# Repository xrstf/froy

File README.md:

# Frøy - ESP8266+BME Hygrometer

This repository contains the source code, schematics and everything else for my
personal fancy homegrown hygrometer (sensor that reports temperature, humidity and
pressure).

## Features

* push or pull mode
* supports BME280, BME680 and BMP280 chips
* programming via USB (only for indoor variant, others need a standalone USB->UART converter)
* webserver with Prometheus compatible `/metrics` endpoint
* reconfiguration via USB or WiFi (i.e. `curl -XPOST -d'{"new":"config"}' http://device/`)
* OTA pull support (Frøy pulls new firmware from a specified location)
* TLS support (single fingerprint only)
* relatively easy to solder by hand (nothing smaller than an 0805 package)

## Mode of Operation

Both indoor and outdoor versions can work in one of two modes:

* **Pull Mode** ("server mode") -- in this mode, Frøy is constantly running and connected
  to your WiFi. It provides an HTTP server and expects you to fetch the data whenever
  you need it (for example via Prometheus).
* **Push Mode** -- in this mode, Frøy will make a measurement, connect to WiFi, send out the
  data to a preconfigured URL and then go to sleep for a configurable amount of time. Rinse
  and repeat.

The advantage of the Pull Mode is that the interval can be centralled controlled (if you have
multiple devices). It also makes it easier to trigger an OTA, as Frøy is constantly listening
for requests.

The advantage of the Push Mode is that Frøy doesn't need any Firewall rules to be reachable
and it saves power (critical for the Outdoor version). Also, indoor versions in Pull Mode would
considerable heat up (an ESP8266 that is connected to WiFi can be 35-40°C) and skew the sensor
readings. So even for indoor versions it is advisable to use Push Mode instead.

While Frøy is not reachable in Push Mode (it never starts a webserver and you'd be pretty luck
to send a request to it the moment it wakes up and before it goes back to sleep), it is still
possible to reconfigurable Frøy remotely by putting the new configuration in the _response_ to
Frøy's push request.

## Flavors

Frøy currently comes in three flavors:

### Frøy Outdoor

This is the original project. It runs using a CR123 battery, which lasts roughly 3-5
months when reporting data every 15 minutes.

The case can be bought on Amazon: https://www.amazon.de/gp/product/B072M2JKGW/ -- I am not
aware of any alternative sources. In case the product disappears, I saved the schematics
in `docs/images/froy-outdoor-case-drawings.jpg`.

### Frøy Indoor

This variant is powered by USB and suitable for indoor use.

### Froy ForMen

This variant is powered by mains voltage and is suitable for locations where changing
the battery regularly is not desirable.

The case can be bought on Amazon, for example https://www.amazon.de/gp/product/B07B9KY9X4/ --
alternatively search for "Snowsound case" on your favorite search engine.

---

Frøy was named after the character in the NRK series ["Norsemen"](https://tv.nrk.no/serie/vikingane).

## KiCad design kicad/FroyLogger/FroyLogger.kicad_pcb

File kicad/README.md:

# KiCad Designs

These designs require that https://github.com/xrstf/kicad-library is set up in your
local KiCad 5 installation.

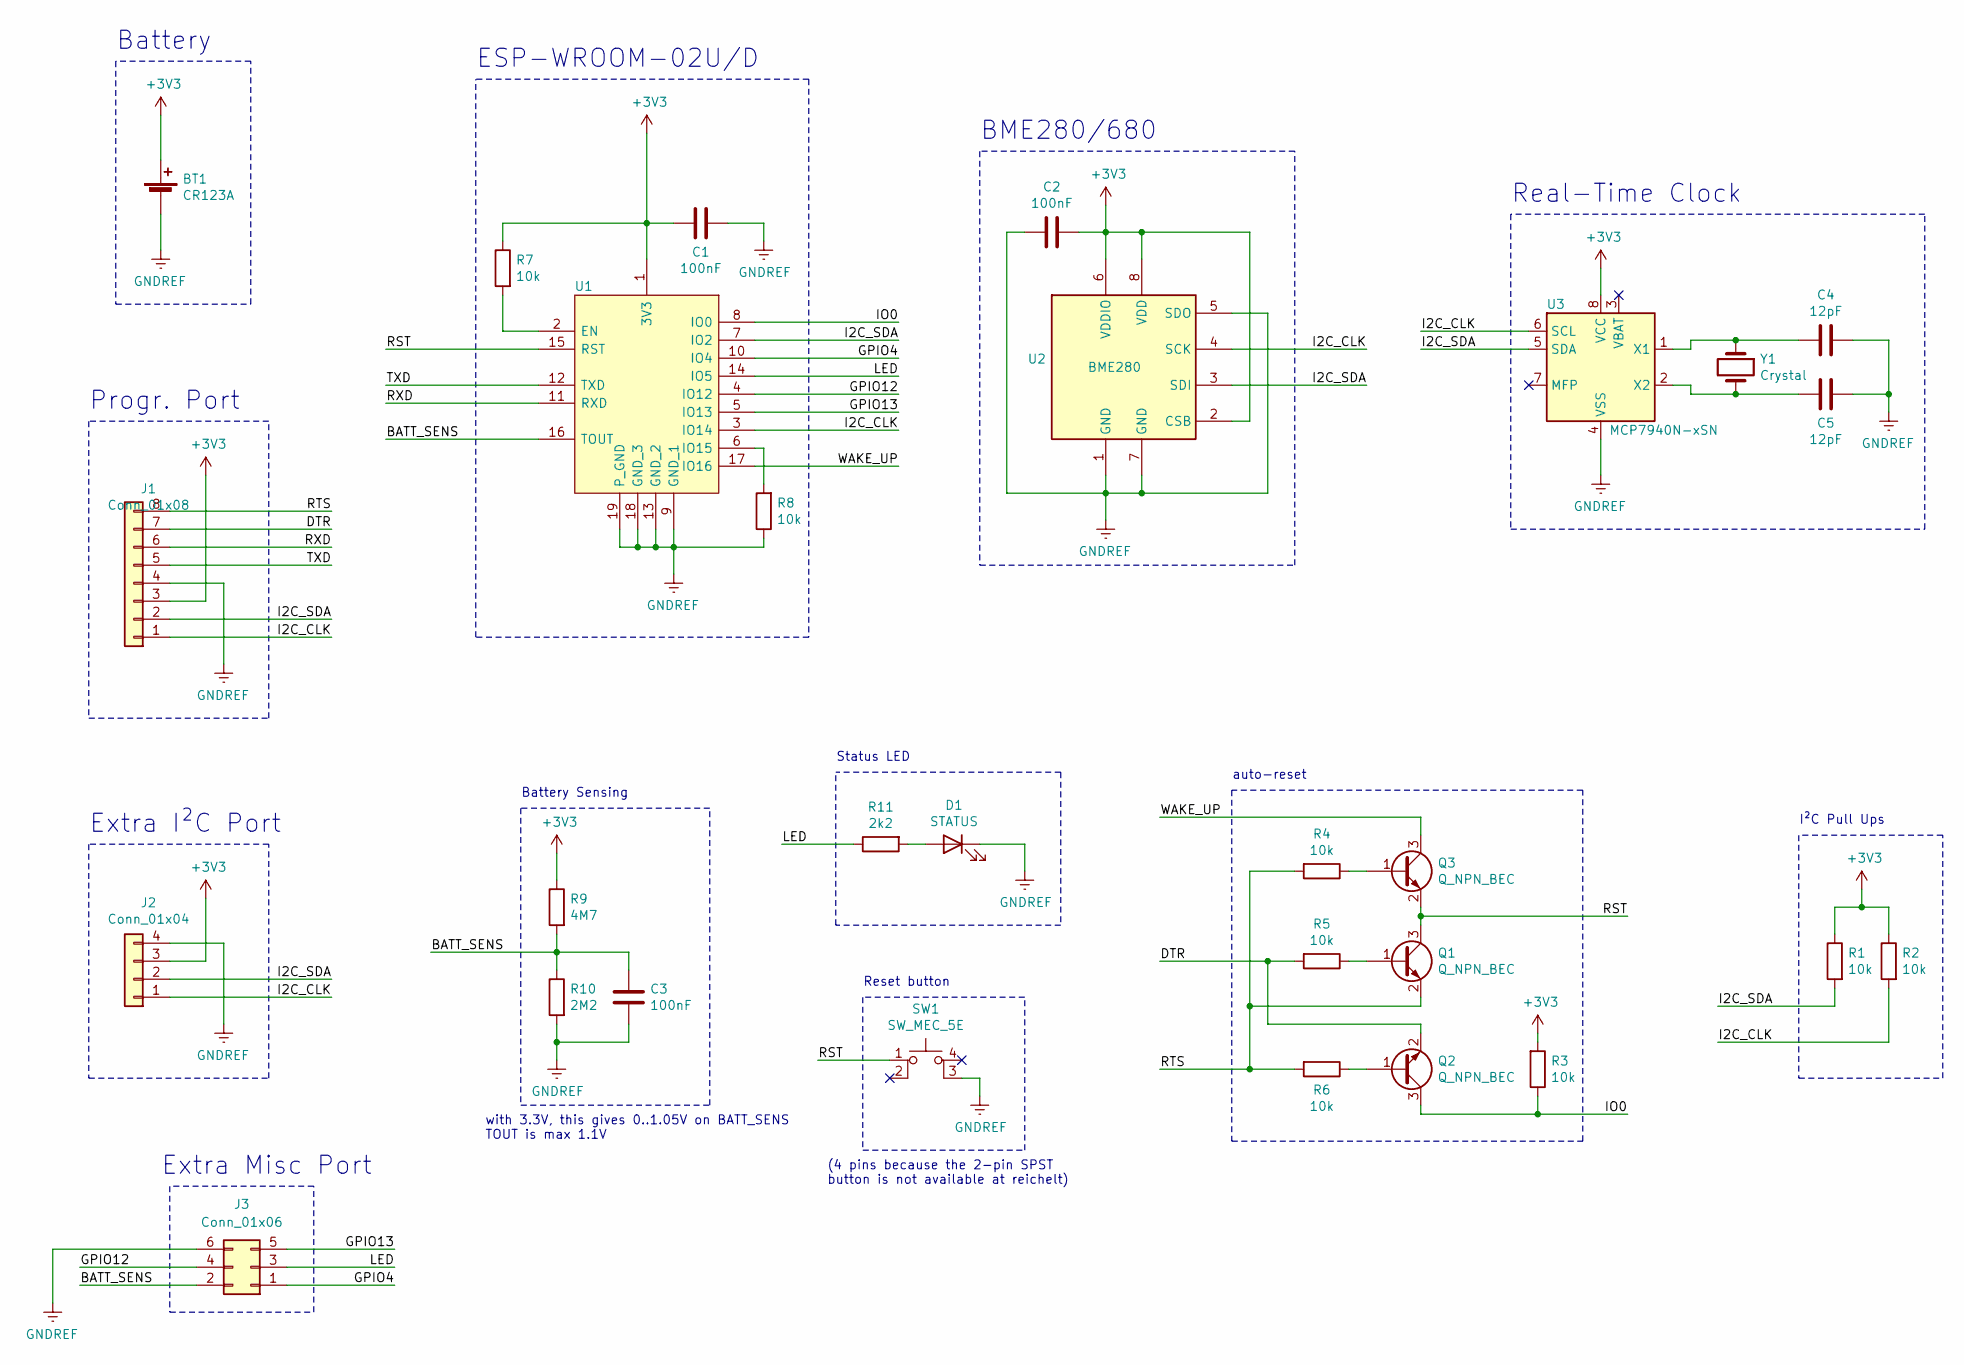
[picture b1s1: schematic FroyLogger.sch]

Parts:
BT1: CR123A; CR123A_Holder_ThroughHole
C1, C2, C3: 100nF; C_0805_2012Metric
C4, C5: 12pF; C_0805_2012Metric
D1: STATUS; LED_0805_2012Metric
J1: Conn_01x08; PinHeader_1x08_P2.54mm_Vertical
J2: Conn_01x04; PinHeader_1x04_P2.54mm_Vertical
J3: Conn_01x06; PinHeader_2x03_P2.54mm_Vertical
Q1, Q2, Q3: Q_NPN_BEC; SOT-23
R1, R2, R3, R4, R5, R6, R7, R8: 10k; R_0805_2012Metric
R9: 4M7; R_0805_2012Metric
R10: 2M2; R_0805_2012Metric
R11: 2k2; R_0805_2012Metric
SW1: SW_MEC_5E; SW_SPST_Omron_B3FS-100xP
U1: ESP-WROOM-02U__4MB_; ESP-WROOM-02U
U2: BME280; BME280_680_BMP280
U3: MCP7940N-xSN; SOIC-8_3.9x4.9mm_P1.27mm
Y1: Crystal; Crystal_SMD_SeikoEpson_MC405-2Pin_9.6x4.1mm

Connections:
+3V3: BT1.1 (+), C1.1, C2.2, J1.3, J2.3, R1.1, R2.1, R3.2, R7.1, R9.1, U1.1 (3V3), U2.2 (CSB), U2.6 (VDDIO), U2.8 (VDD), U3.8 (VCC)
/BATT_SENS: C3.2, J3.2, R9.2, R10.1, U1.16 (TOUT)
/DTR: J1.7, Q2.2 (E), R5.2
/GPIO4: J3.1, U1.10 (IO4)
/GPIO12: J3.4, U1.4 (IO12)
/GPIO13: J3.5, U1.5 (IO13)
/I2C_CLK: J1.1, J2.1, R2.2, U1.3 (IO14), U2.4 (SCK), U3.6 (SCL)
/I2C_SDA: J1.2, J2.2, R1.2, U1.7 (IO2), U2.3 (SDI), U3.5 (SDA)
/IO0: Q2.3 (C), R3.1, U1.8 (IO0)
/LED: J3.3, R11.1, U1.14 (IO5)
/RST: Q1.3 (C), Q3.2 (E), SW1.1, U1.15 (RST)
/RTS: J1.8, Q1.2 (E), R4.2, R6.2
/RXD: J1.6, U1.11 (RXD)
/TXD: J1.5, U1.12 (TXD)
/WAKE_UP: Q3.3 (C), U1.17 (IO16)
GNDREF: BT1.2 (-), C1.2, C2.1, C3.1, C4.2, C5.2, D1.1 (K), J1.4, J2.4, J3.6, R8.1, R10.2, SW1.3 (K), U1.9 (GND_1), U1.13 (GND_2), U1.18 (GND_3), U1.19 (P_GND), U2.1 (GND), U2.5 (SDO), U2.7 (GND), U3.4 (VSS)
unnamed: C4.1, U3.1 (X1), Y1.1
unnamed: C5.1, U3.2 (X2), Y1.2
unnamed: D1.2 (A), R11.2
unnamed: Q1.1 (B), R5.1
unnamed: Q2.1 (B), R6.1
unnamed: Q3.1 (B), R4.1
unnamed: R7.2, U1.2 (EN)
unnamed: R8.2, U1.6 (IO15)

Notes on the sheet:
Status LED
auto-reset
ESP-WROOM-02U/D
Reset button
BME280/680
I²C Pull Ups
Battery
Progr. Port
Battery Sensing
with 3.3V, this gives 0..1.05V on BATT_SENS TOUT is max 1.1V
(4 pins because the 2-pin SPST button is not available at reichelt)
Real-Time Clock
Extra I²C Port
Extra Misc Port

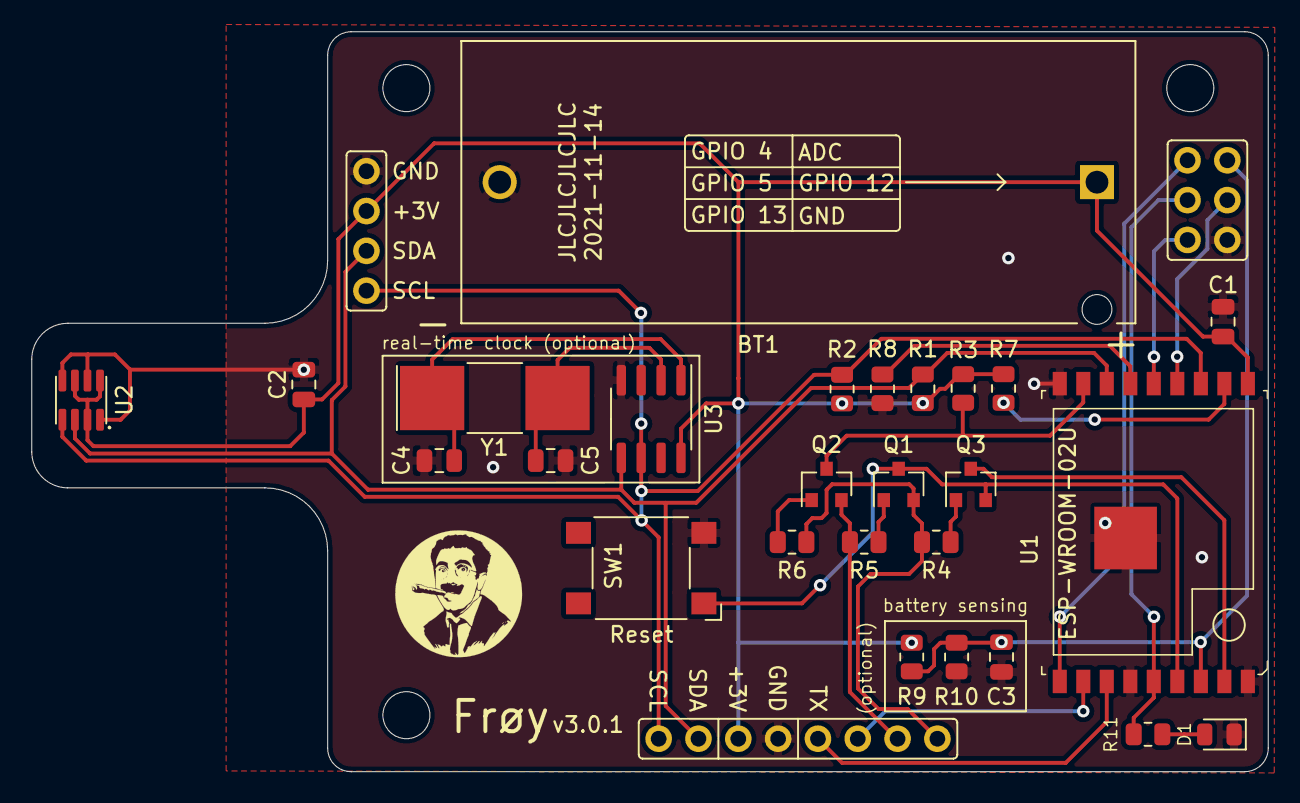
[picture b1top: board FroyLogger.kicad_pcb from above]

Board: 2 copper layers, 78.9 x 47.2 mm, 33 parts (0 on the bottom side), 24 nets.

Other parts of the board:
G1: LOGO; groucho
H1: NW; MountingHole_3mm
H2: NE; MountingHole_3mm
H4: SW; MountingHole_3mm

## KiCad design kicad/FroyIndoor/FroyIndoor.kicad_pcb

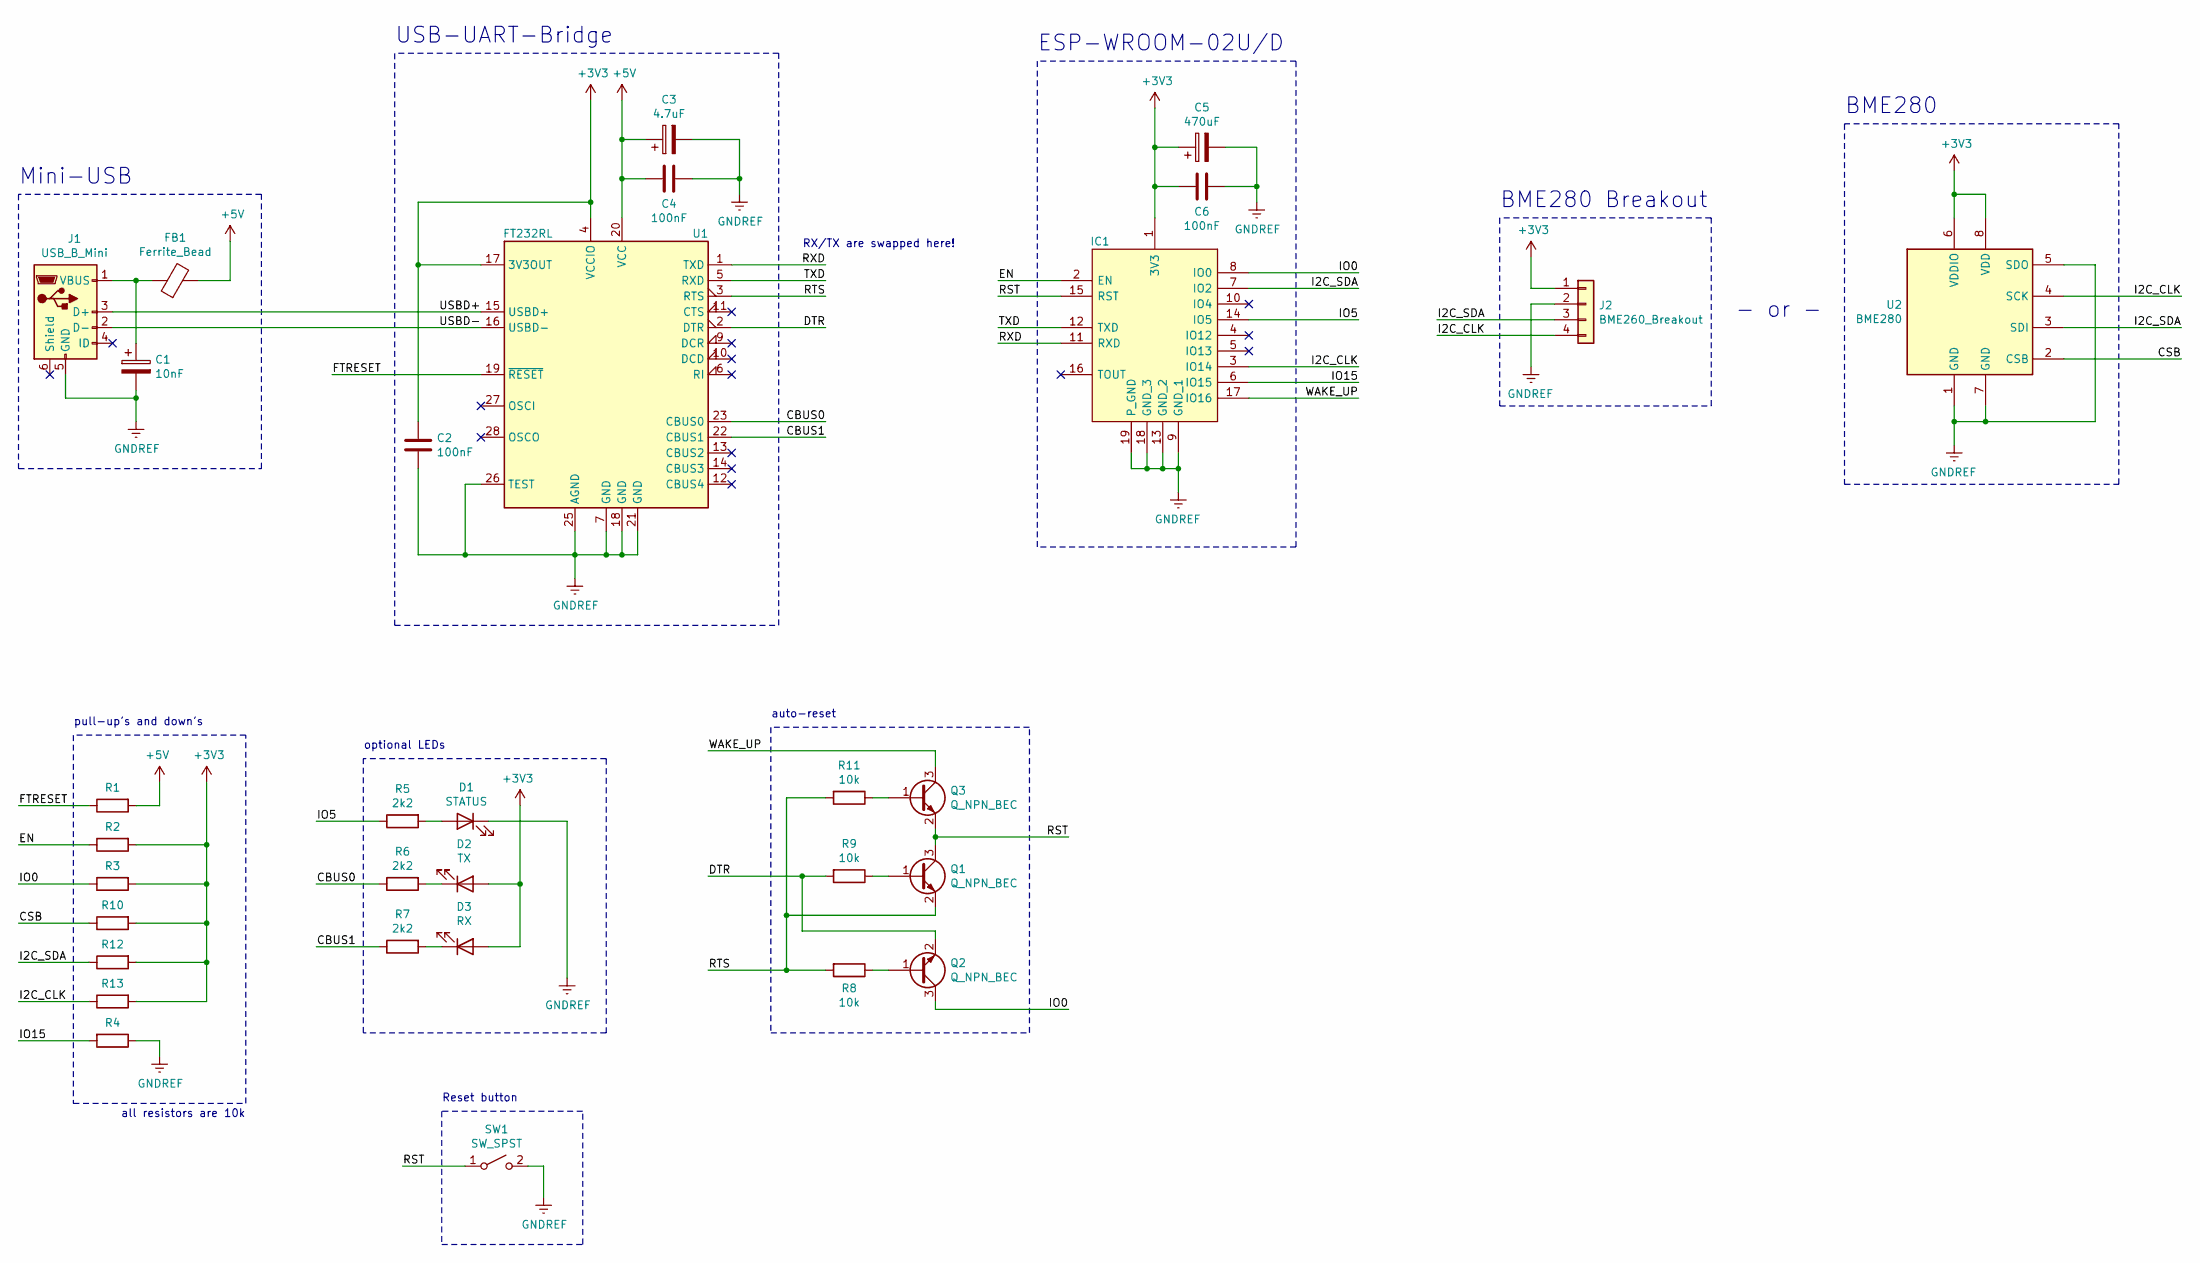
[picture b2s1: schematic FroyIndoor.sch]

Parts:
C1: 10nF; C_1206_3216Metric_Pad1.42x1.75mm_HandSolder
C2, C4, C6: 100nF; C_1206_3216Metric_Pad1.42x1.75mm_HandSolder
C3: 4.7uF; C_1206_3216Metric_Pad1.42x1.75mm_HandSolder
C5: 470uF; CP_Elec_10x12.5
D1: STATUS; LED_1206_3216Metric_Pad1.42x1.75mm_HandSolder
D2: TX; LED_1206_3216Metric_Pad1.42x1.75mm_HandSolder
D3: RX; LED_1206_3216Metric_Pad1.42x1.75mm_HandSolder
FB1: Ferrite_Bead; L_1206_3216Metric_Pad1.42x1.75mm_HandSolder
IC1: ESP-WROOM-02U__4MB_; ESP-WROOM-02U
J1: USB_B_Mini; USB_BWM_MIniUSB_THT_reichelt
J2: BME260_Breakout; PinHeader_1x04_P2.54mm_Vertical
Q1, Q2, Q3: Q_NPN_BEC; SOT-23
R1, R2, R3, R4, R8, R9, R10, R11, R12, R13: 10k; R_1206_3216Metric_Pad1.42x1.75mm_HandSolder
R5, R6, R7: 2k2; R_1206_3216Metric_Pad1.42x1.75mm_HandSolder
SW1: SW_SPST; SW_Tactile_SPST_Angled_PTS645Vx83-2LFS
U1: FT232RL; SSOP-28_5.3x10.2mm_P0.65mm
U2: BME280; BME280_680_BMP280

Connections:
+3V3: C2.1, C5.1, C6.1, D2.2 (A), D3.2 (A), IC1.1 (3V3), J2.1, R2.2, R3.2, R10.2, R12.2, R13.2, U1.4 (VCCIO), U1.17 (3V3OUT), U2.6 (VDDIO), U2.8 (VDD)
+5V: C3.1, C4.1, FB1.2, R1.2, U1.20 (VCC)
/CBUS0: R6.1, U1.23 (CBUS0)
/CBUS1: R7.1, U1.22 (CBUS1)
/CSB: R10.1, U2.2 (CSB)
/DTR: Q2.2 (E), R9.2, U1.2 (DTR)
/EN: IC1.2 (EN), R2.1
/FTRESET: R1.1, U1.19 (~RESET~)
/I2C_CLK: IC1.3 (IO14), J2.4, R13.1, U2.4 (SCK)
/I2C_SDA: IC1.7 (IO2), J2.3, R12.1, U2.3 (SDI)
/IO0: IC1.8 (IO0), Q2.3 (C), R3.1
/IO5: IC1.14 (IO5), R5.1
/IO15: IC1.6 (IO15), R4.2
/RST: IC1.15 (RST), Q1.3 (C), Q3.2 (E), SW1.1 (A)
/RTS: Q1.2 (E), R8.2, R11.2, U1.3 (RTS)
/RXD: IC1.11 (RXD), U1.1 (TXD)
/TXD: IC1.12 (TXD), U1.5 (RXD)
/USBD+: J1.3 (D+), U1.15 (USBD+)
/USBD-: J1.2 (D-), U1.16 (USBD-)
/WAKE_UP: IC1.17 (IO16), Q3.3 (C)
GNDREF: C1.2, C2.2, C3.2, C4.2, C5.2, C6.2, D1.1 (K), IC1.9 (GND_1), IC1.13 (GND_2), IC1.18 (GND_3), IC1.19 (P_GND), J1.5 (GND), J2.2, R4.1, SW1.2 (B), U1.7 (GND), U1.18 (GND), U1.21 (GND), U1.25 (AGND), U1.26 (TEST), U2.1 (GND), U2.5 (SDO), U2.7 (GND)
unnamed: C1.1, FB1.1, J1.1 (VBUS)
unnamed: D1.2 (A), R5.2
unnamed: D2.1 (K), R6.2
unnamed: D3.1 (K), R7.2
unnamed: Q1.1 (B), R9.1
unnamed: Q2.1 (B), R8.1
unnamed: Q3.1 (B), R11.1

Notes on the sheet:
USB-UART-Bridge
Mini-USB
optional LEDs
auto-reset
pull-up's and down's
all resistors are 10k
RX/TX are swapped here!
ESP-WROOM-02U/D
BME280 Breakout
Reset button
BME280
- or -

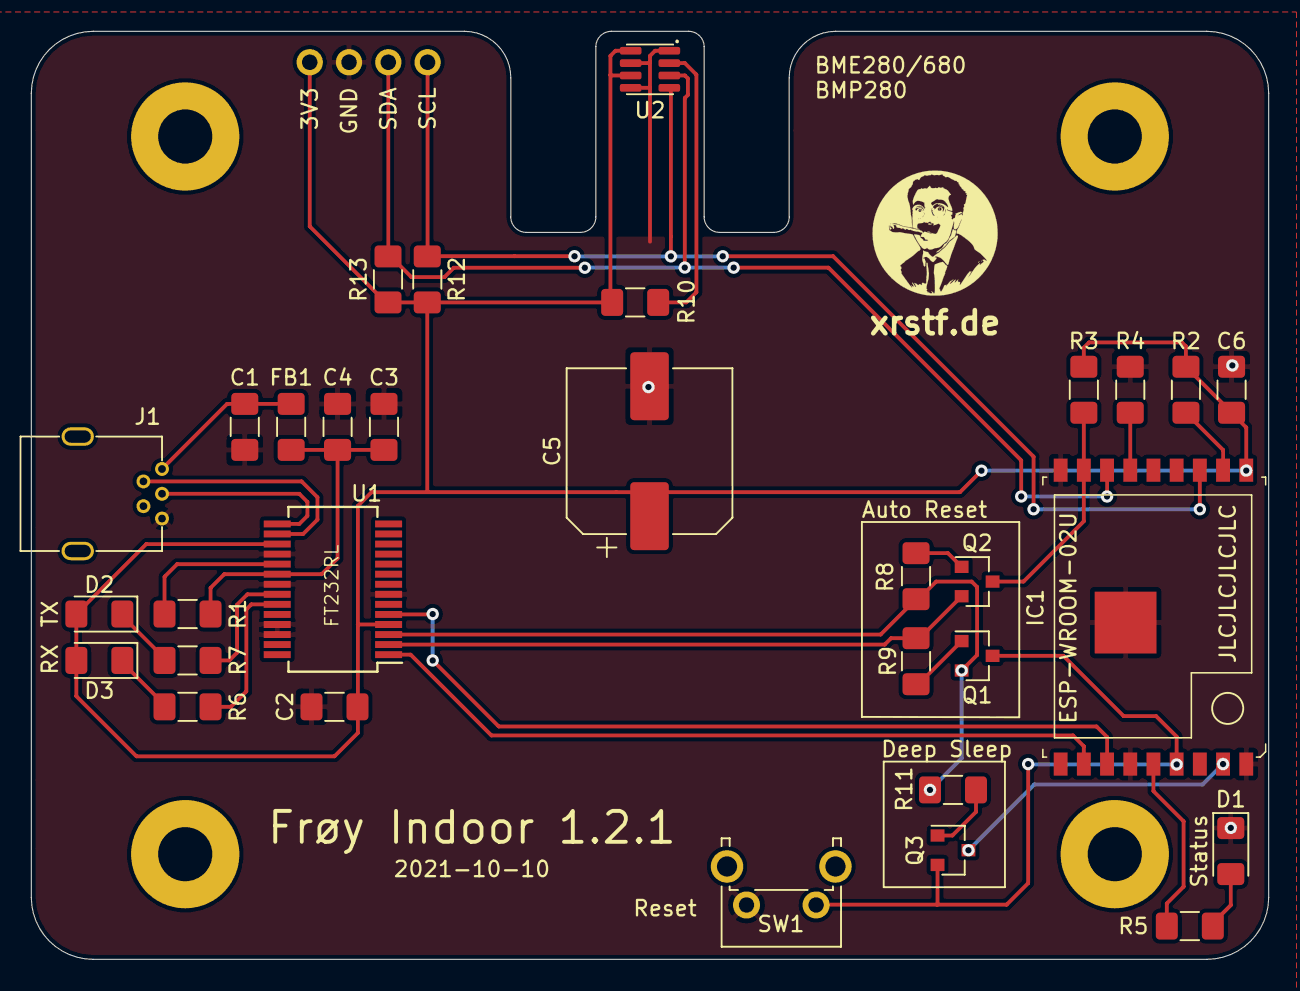
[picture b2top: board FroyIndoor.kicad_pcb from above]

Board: 2 copper layers, 80.0 x 60.0 mm, 32 parts (0 on the bottom side), 28 nets.

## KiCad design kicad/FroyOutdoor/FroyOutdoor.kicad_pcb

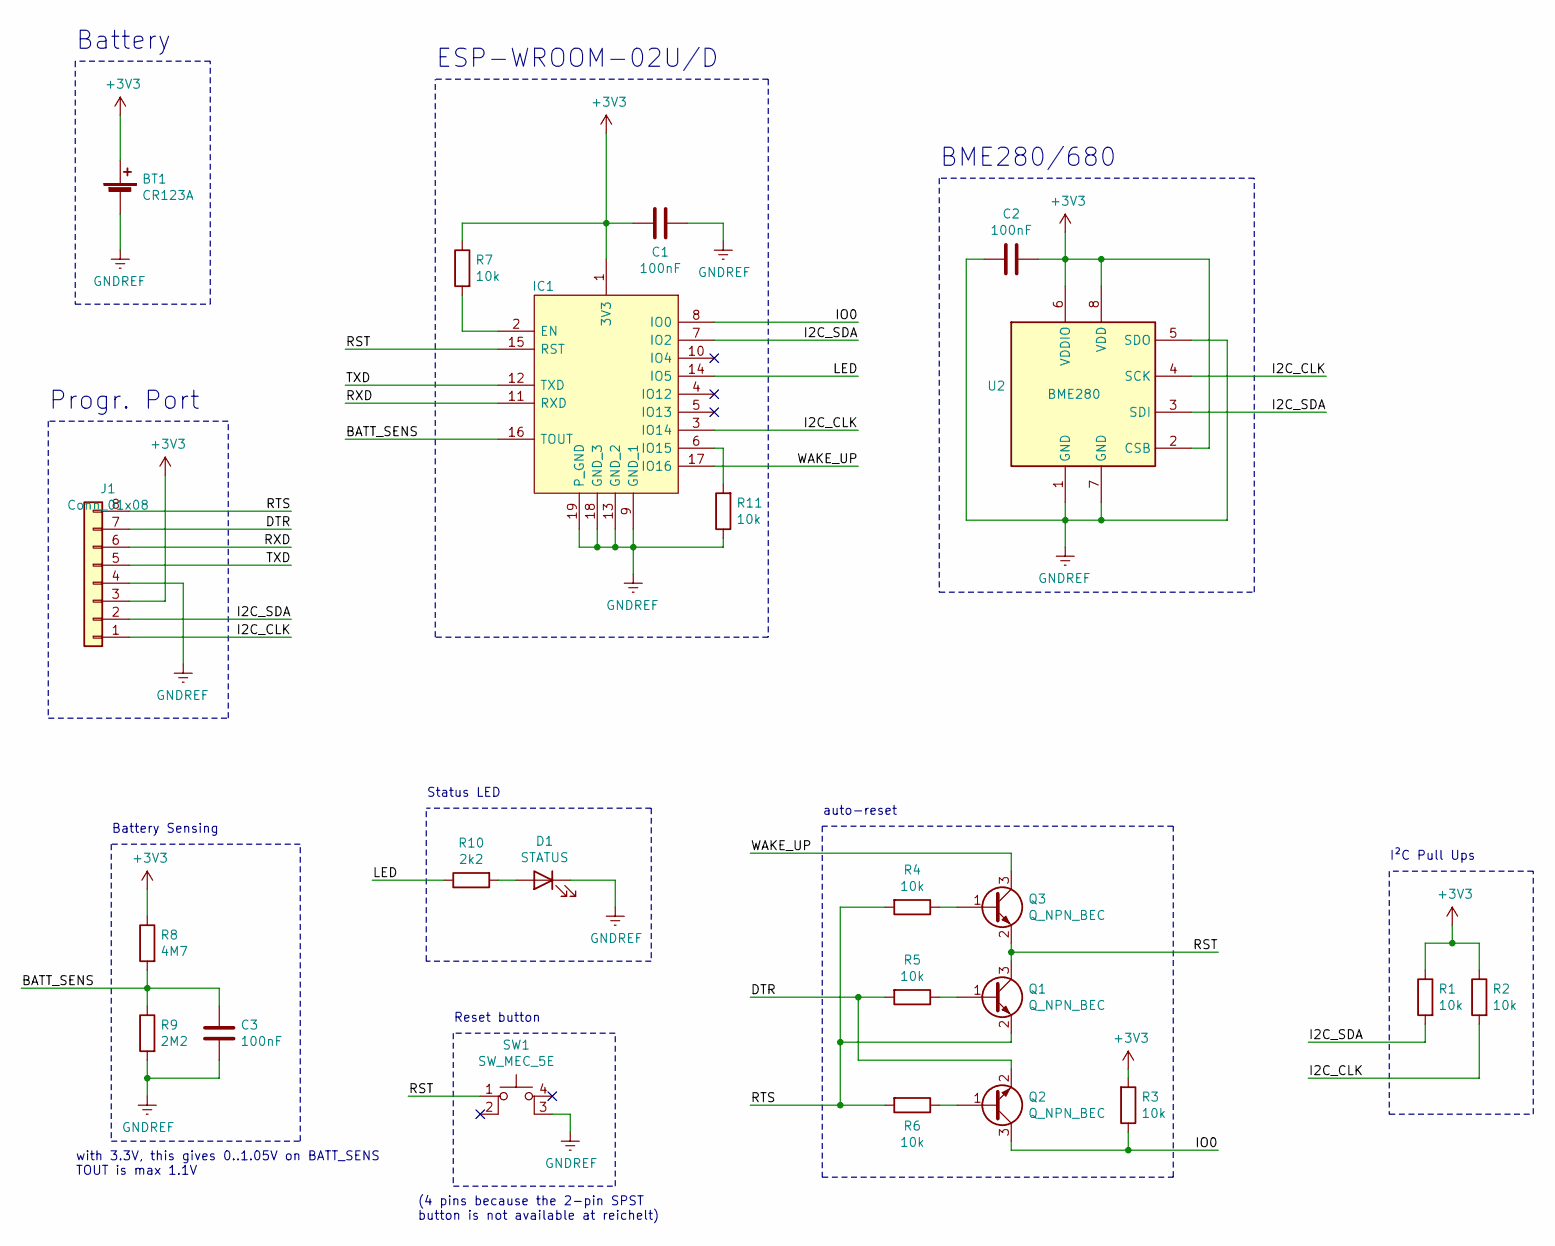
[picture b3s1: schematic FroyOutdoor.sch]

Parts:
BT1: CR123A; CR123A_Holder_ThroughHole
C1, C2, C3: 100nF; C_0805_2012Metric
D1: STATUS; LED_0805_2012Metric
IC1: ESP-WROOM-02U__4MB_; ESP-WROOM-02U
J1: Conn_01x08; PinHeader_1x08_P2.54mm_Vertical
Q1, Q2, Q3: Q_NPN_BEC; SOT-23
R1, R2, R3, R4, R5, R6, R7, R11: 10k; R_0805_2012Metric
R8: 4M7; R_0805_2012Metric
R9: 2M2; R_0805_2012Metric
R10: 2k2; R_0805_2012Metric
SW1: SW_MEC_5E; SW_SPST_Omron_B3FS-100xP
U2: BME280; BME280_680_BMP280

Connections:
+3V3: BT1.1 (+), C1.1, C2.2, IC1.1 (3V3), J1.3, R1.1, R2.1, R3.2, R7.1, R8.1, U2.2 (CSB), U2.6 (VDDIO), U2.8 (VDD)
/BATT_SENS: C3.2, IC1.16 (TOUT), R8.2, R9.1
/DTR: J1.7, Q2.2 (E), R5.2
/I2C_CLK: IC1.3 (IO14), J1.1, R2.2, U2.4 (SCK)
/I2C_SDA: IC1.7 (IO2), J1.2, R1.2, U2.3 (SDI)
/IO0: IC1.8 (IO0), Q2.3 (C), R3.1
/LED: IC1.14 (IO5), R10.1
/RST: IC1.15 (RST), Q1.3 (C), Q3.2 (E), SW1.1
/RTS: J1.8, Q1.2 (E), R4.2, R6.2
/RXD: IC1.11 (RXD), J1.6
/TXD: IC1.12 (TXD), J1.5
/WAKE_UP: IC1.17 (IO16), Q3.3 (C)
GNDREF: BT1.2 (-), C1.2, C2.1, C3.1, D1.1 (K), IC1.9 (GND_1), IC1.13 (GND_2), IC1.18 (GND_3), IC1.19 (P_GND), J1.4, R9.2, R11.1, SW1.3 (K), U2.1 (GND), U2.5 (SDO), U2.7 (GND)
unnamed: D1.2 (A), R10.2
unnamed: IC1.2 (EN), R7.2
unnamed: IC1.6 (IO15), R11.2
unnamed: Q1.1 (B), R5.1
unnamed: Q2.1 (B), R6.1
unnamed: Q3.1 (B), R4.1

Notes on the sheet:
Status LED
auto-reset
ESP-WROOM-02U/D
Reset button
BME280/680
I²C Pull Ups
Battery
Progr. Port
Battery Sensing
with 3.3V, this gives 0..1.05V on BATT_SENS TOUT is max 1.1V
(4 pins because the 2-pin SPST button is not available at reichelt)

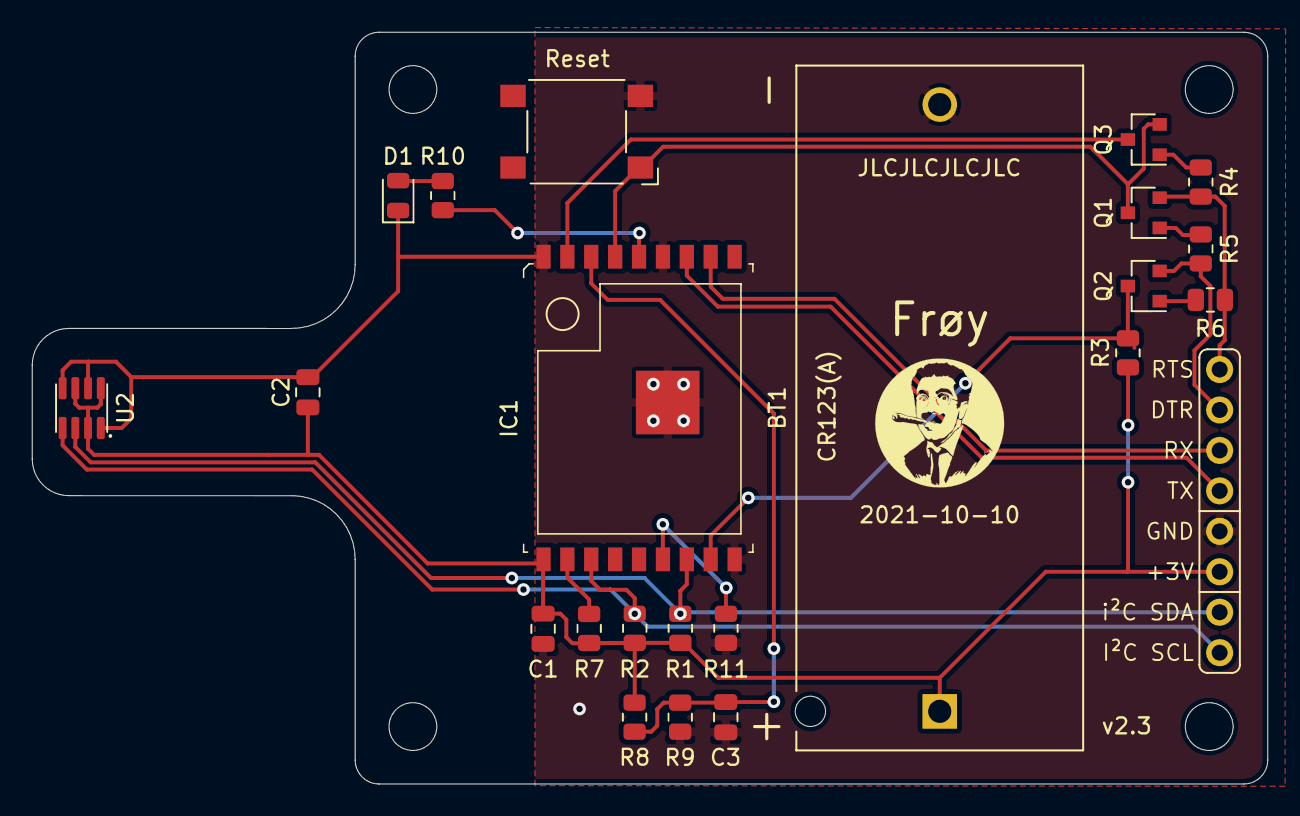
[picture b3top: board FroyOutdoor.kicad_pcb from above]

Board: 2 copper layers, 77.6 x 47.2 mm, 27 parts (0 on the bottom side), 19 nets.

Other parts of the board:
H1: NW; MountingHole_3mm
H2: NE; MountingHole_3mm
H3: SE; MountingHole_3mm
H4: SW; MountingHole_3mm

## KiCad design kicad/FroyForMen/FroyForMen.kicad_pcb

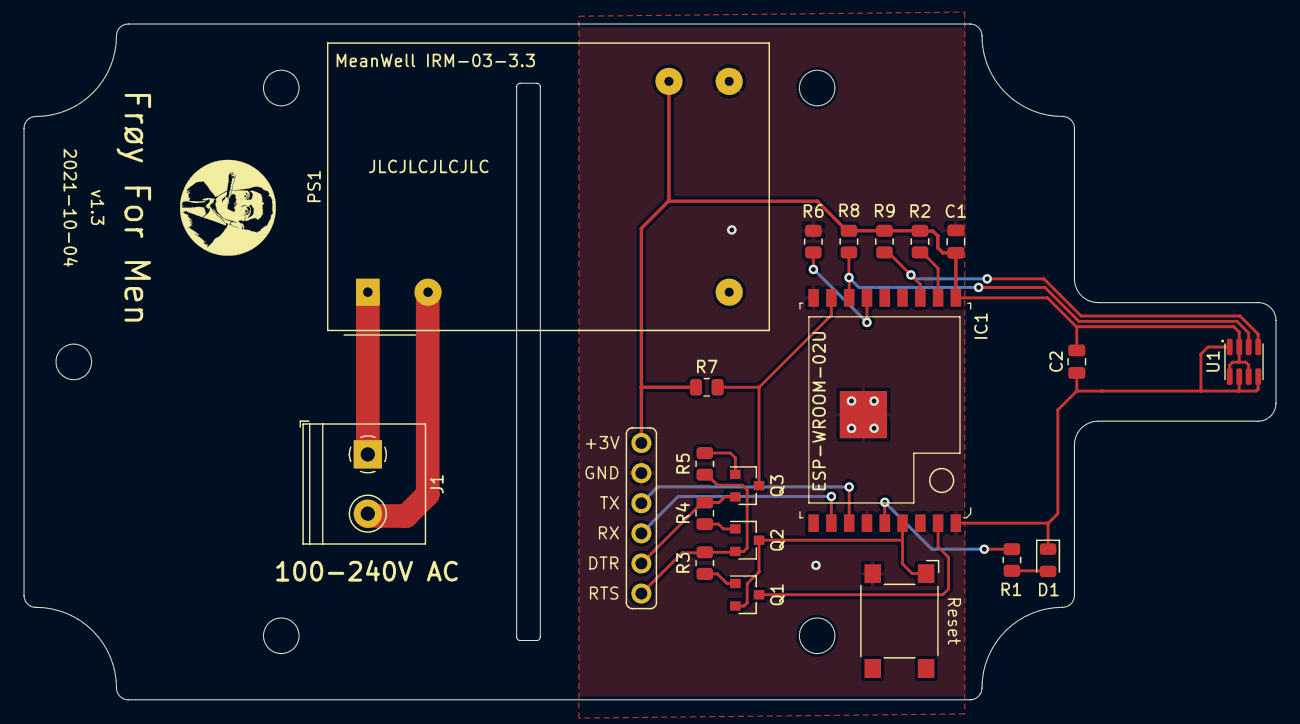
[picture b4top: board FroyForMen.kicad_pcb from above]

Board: 2 copper layers, 105.6 x 57.0 mm, 26 parts (0 on the bottom side), 20 nets.

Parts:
C1, C2: 100nF; C_0805_2012Metric
D1: STATUS; LED_0805_2012Metric
H1: NW; MountingHole_3mm
H4, H4#2, H4#3, H4#4: SW; MountingHole_3mm
IC1: ESP-WROOM-02U__4MB_; ESP-WROOM-02U
J1: Screw_Terminal_01x02; TerminalBlock_Philmore_TB132_1x02_P5.00mm_Horizontal
J2: Conn_01x06; PinHeader_1x06_P2.54mm_Vertical
PS1: IRM-03-3.3; Converter_ACDC_MeanWell_IRM-03-xx_THT
Q1, Q2, Q3: Q_NPN_BEC; SOT-23
R1: 2k2; R_0805_2012Metric
R2, R3, R4, R5, R6, R7, R8, R9: 10k; R_0805_2012Metric
SW1: SW_MEC_5E; SW_SPST_Omron_B3FS-100xP
U1: BME280; BME280_680_BMP280

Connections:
+3V3: C1.1, C2.2, IC1.1, J2.1, PS1.16, R2.1, R7.2, R8.1, R9.1, U1.2, U1.6, U1.8
/AC_L: J1.1, PS1.1
/AC_N: J1.2, PS1.3
/DTR: J2.5, Q3.2, R4.2
/I2C_CLK: IC1.3, R9.2, U1.4
/I2C_SDA: IC1.7, R8.2, U1.3
/IO0: IC1.8, Q3.3, R7.1
/LED: IC1.14, R1.1
/RST: IC1.15, Q1.2, Q2.3, SW1.1
/RTS: J2.6, Q2.2, R3.2, R5.2
/RXD: IC1.11, J2.4
/TXD: IC1.12, J2.3
/WAKE_UP: IC1.17, Q1.3
GNDREF: C1.2, C2.1, D1.1, IC1.9, IC1.13, IC1.18, IC1.19, J2.2, PS1.14, R6.1, SW1.3, U1.1, U1.5, U1.7
unnamed: D1.2, R1.2
unnamed: IC1.2, R2.2
unnamed: IC1.6, R6.2
unnamed: Q1.1, R3.1
unnamed: Q2.1, R4.1
unnamed: Q3.1, R5.1

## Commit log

2021-08-21 initial import
    * FroyIndoor 1.2
    * FroyForMen rev 2
    * FroyOutdoor 2.0
2021-08-21 add readme
2021-08-21 add PCB renders
2021-08-21 add some photos
2021-08-21 extend readme
2021-08-21 add source code v4.1
2021-08-21 add links to amazon for the cases
2021-08-21 add datasheets
2021-08-21 fix typo
2021-08-21 add name hint
2021-08-21 add hack stuff
2021-09-12 add clang-format
2021-09-12 better HTTP UA, setup BME280 sensors and use forced mode instead of permanent sampling (normal) mode
2021-09-12 version 4.2
2021-09-13 Froy Outdoor 2.1, now with transistor controlling sensor and battery measurement
2021-09-13 do not make a distinction between has-battery and has-no-battery, likewise for the power transistor
2021-09-13 clang-format
2021-09-24 FroyOutdoor v2.2 - removed power transistor again, used Omron button
2021-09-24 remove concept of power transistor from the codebase
2021-09-26 set TCP timeout and do not use keep-alives in push mode
2021-10-04 FroyForMen v1.3 - removed power transistor, use Omron button
2021-10-09 fix a couple of typos
2021-10-09 FroyOutdoor v2.3 - expose I2C SDA/SCL pins to make it easy to reuse the board for quick experiments with other breakout boards
2021-10-10 FroyIndoor v1.2.1 - fix silk screen for the I2C pins, use more common resistor values
2021-10-17 save bytes by making the push payload use cryptic short key names
2021-10-17 bump version to 4.5
2021-10-23 add FroyLogger, with a realtime clock and much more exposed GPIO pins to serve as a nice WiFi-enabled datalogger
2021-11-13 add clock implementation
2021-11-13 EEPROM data v3, adding timeseries fields
2021-11-13 implement most of the initial datalogging mode
2021-11-13 cleanup
2021-11-13 implement maxDataPoints for data logging mode
2021-11-13 check WiFi status more frequently
2021-11-13 nicer config output
2021-11-14 FroyLogger 3.0.1, better crystal footprint
2021-11-17 fix junk output at dumping a time series
2021-11-18 add batch upload option to data logging mode
2021-11-19 do datalogging in binary, allow changing datalogging settings via HTTP response
2021-12-06 better config info
2021-12-12 add clear-all-time-series command
2021-12-20 time.nist.gov is very unreliable
2021-12-21 update NTP every time we connect to WiFi
2022-01-29 make startup delay configurable
